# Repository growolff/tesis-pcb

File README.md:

View this project on [CADLAB.io](https://cadlab.io/project/1032). 

# tesis-pcb
Sch and Brd files of the PCBs generated in the thesis proyect.

## PSOC Pinout
PSOC CY8CKIT-059 inputs and outputs
  
| Pin | Motor | Function | A/D  | I/O |
| --- | ----- | -------- |  --- | --- |
| 12:0|   PM1 |   BRAKEN |  D   | O   |
| 12:1|   PM1 |   DIR    |  D   | O   |
| 12:2|   PM1 |   ENABLE |  D   | O   |
| 3:0 |   PM1 |   SPEED  |  A   | O   |
| 0:0 |   PM1 |   TENSION|  A   | I   |
| 2:4 |   PM1 |   HA     |  D   | I   | 
| 2:5 |   PM1 |   HB     |  D   | I   |
| 1:4 |   PM2 |   BRAKEN |  D   | O   |
| 1:5 |   PM2 |   DIR    |  D   | O   |
| 1:6 |   PM2 |   ENABLE |  D   | O   |
| 3:1 |   PM2 |   SPEED  |  A   | O   |
| 2:6 |   PM2 |   HA     |  D   | I   | 
| 2:7 |   PM2 |   HB     |  D   | I   |

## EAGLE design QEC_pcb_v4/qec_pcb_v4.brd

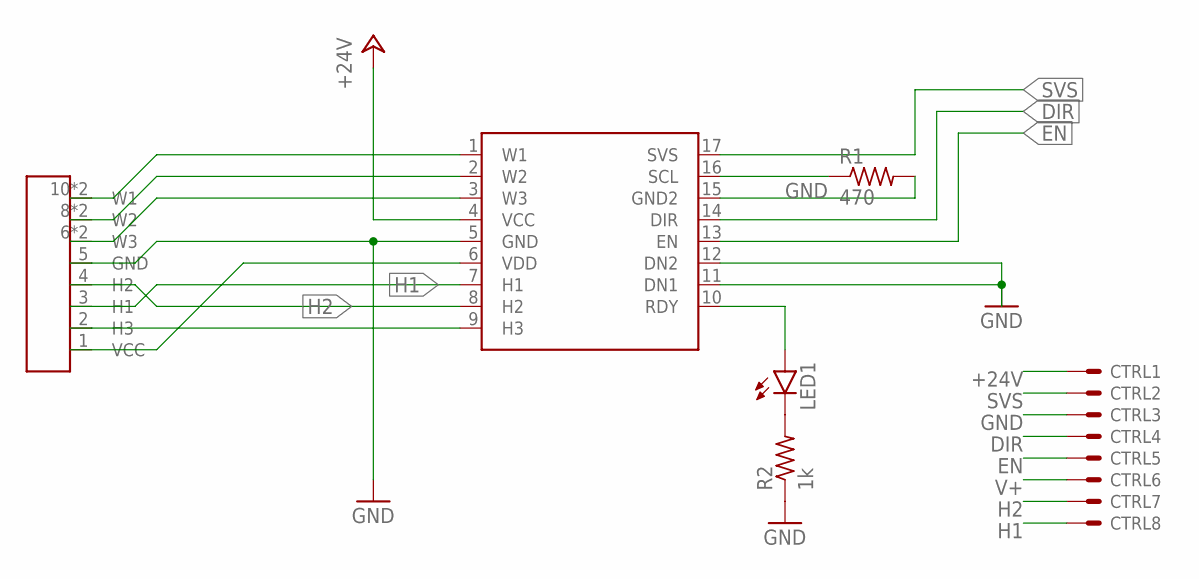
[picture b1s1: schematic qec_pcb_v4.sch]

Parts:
CTRL: JST8; JST
DEC: 1-Q-EC1-Q-EC-SMD; 1-Q-EC-SMD
LED1: LEDCHIPLED_0805; CHIPLED_0805
MOTOR: 68611114122
R1: 470; M0805
R2: 1k; M0805

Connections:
+24V: CTRL.1, DEC.4 (VCC)
DIR: CTRL.4, DEC.14 (DIR)
EN: CTRL.5, DEC.13 (EN)
GND: CTRL.3, DEC.5 (GND), DEC.11 (DN1), DEC.12 (DN2), DEC.15 (GND2), MOTOR.5 (GND), R1.2, R2.1
H1: CTRL.8, DEC.7 (H1), MOTOR.3 (H1)
H2: CTRL.7, DEC.8 (H2), MOTOR.4 (H2)
unnamed: LED1.C, R2.2
unnamed: DEC.10 (RDY), LED1.A
unnamed: DEC.1 (W1), MOTOR.10 (W1), MOTOR.11 (W1)
unnamed: DEC.16 (SCL), R1.1
unnamed: DEC.2 (W2), MOTOR.8 (W2), MOTOR.9 (W2)
unnamed: DEC.3 (W3), MOTOR.6 (W3), MOTOR.7 (W3)
unnamed: DEC.9 (H3), MOTOR.2 (H3)
SVS: CTRL.2, DEC.17 (SVS)
V+: CTRL.6, DEC.6 (VDD), MOTOR.1 (VCC)

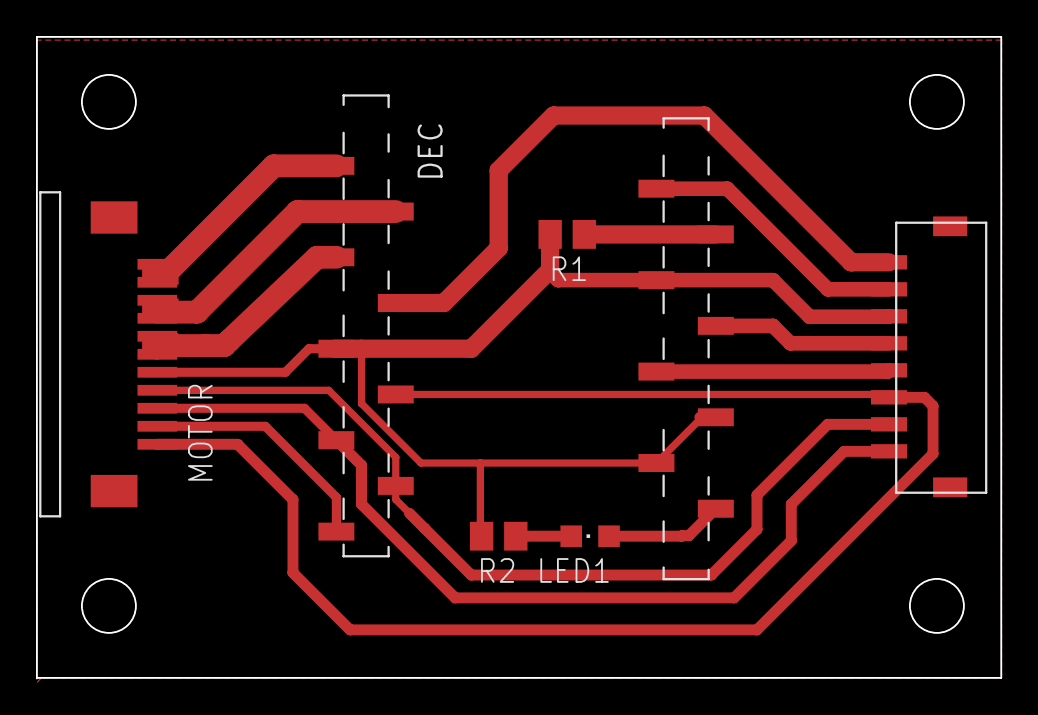
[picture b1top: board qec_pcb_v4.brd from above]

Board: 2 copper layers, 53.6 x 35.6 mm, 6 parts (0 on the bottom side), 15 nets.

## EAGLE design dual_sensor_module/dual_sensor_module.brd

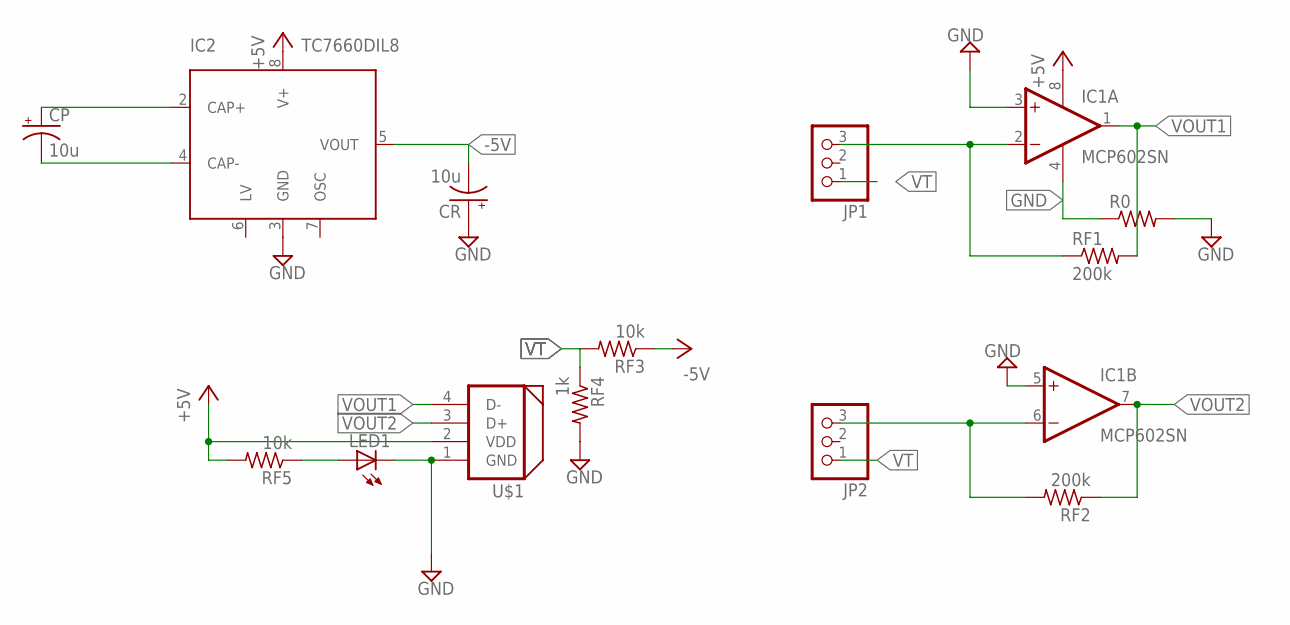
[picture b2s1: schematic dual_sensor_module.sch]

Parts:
CP: 10u; E2,5-5
CR: 10u; E2,5-5
IC1: MCP602SN; SO08
IC2: TC7660DIL8; DIL8
JP1, JP2: PINHD-1X3; 1X03
LED1: LEDCHIPLED_0805; CHIPLED_0805
R0: R-US_R1206; R1206
RF1, RF2: 200k; R0805
RF3, RF5: 10k; R0805
RF4: 1k; R0805
U$1: DYNAMIXEL_RS485; DYNAMIXEL_SPOX_04

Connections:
+5V: IC1.8 (V+), IC2.8 (V+), RF5.2, U$1.2 (VDD)
-5V: CR.-, IC2.5 (VOUT), RF3.1
GND: CR.+, IC1.3 (+IN), IC1.4 (V-), IC1.5 (+IN), IC2.3 (GND), LED1.C, R0.1, R0.2, RF4.2, U$1.1 (GND)
unnamed: CP.+, IC2.2 (CAP+)
unnamed: CP.-, IC2.4 (CAP-)
unnamed: LED1.A, RF5.1
unnamed: IC1.2 (-IN), JP1.3, RF1.1
unnamed: IC1.6 (-IN), JP2.3, RF2.2
VOUT1: IC1.1 (OUT), RF1.2, U$1.4 (D-)
VOUT2: IC1.7 (OUT), RF2.1, U$1.3 (D+)
VT: JP1.1, JP2.1, RF3.2, RF4.1

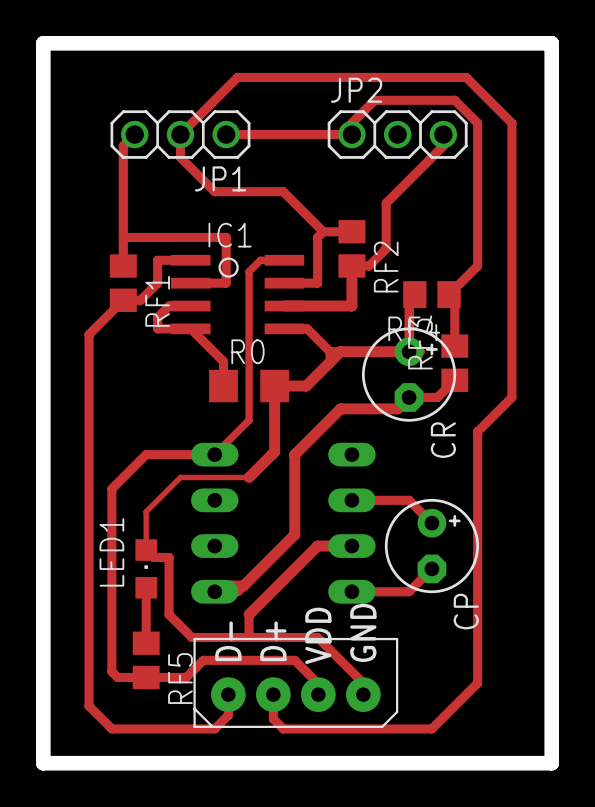
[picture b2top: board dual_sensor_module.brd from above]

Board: 2 copper layers, 28.2 x 40.0 mm, 14 parts (1 on the bottom side), 11 nets.

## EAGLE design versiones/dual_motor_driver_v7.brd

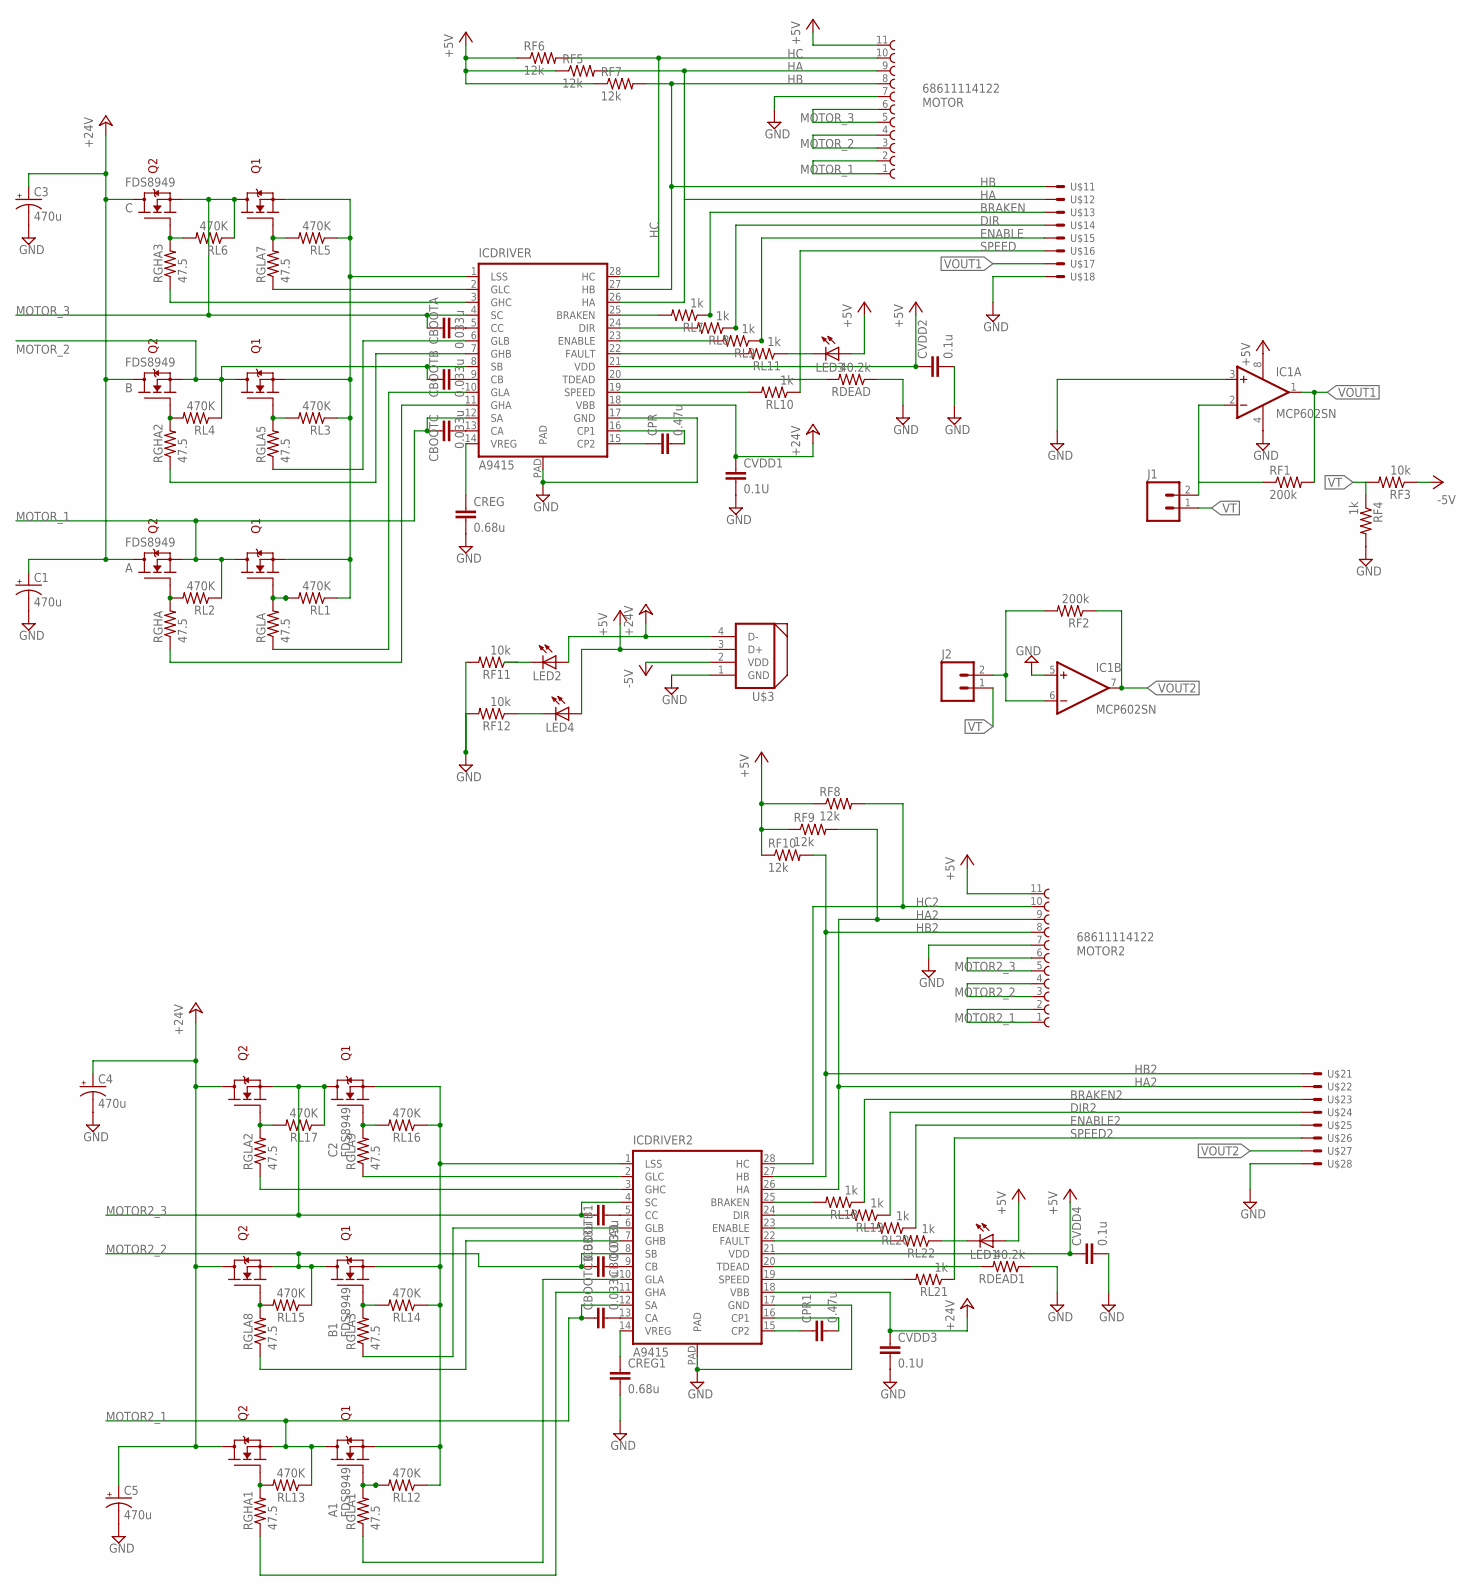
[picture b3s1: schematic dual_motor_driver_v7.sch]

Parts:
A, A1: FDS8949; SOIC8
B, B1: FDS8949; SOIC8
C, C2: FDS8949; SOIC8
C1, C3, C4, C5: 470u; 140CLH-1010
CBOOTA, CBOOTA1: 0.033u; C0805
CBOOTB, CBOOTB1: 0.033u; C0805
CBOOTC, CBOOTC1: 0.033u; C0805
CPR, CPR1: 0.47u; C0805
CREG, CREG1: 0.68u; C0805
CVDD1, CVDD3: 0.1U; C0805
CVDD2, CVDD4: 0.1u; C0805
IC1: MCP602SN; SO08
ICDRIVER, ICDRIVER2: A9415; TSSOP28
J1, J2: M02PTH; 1X02
LED1, LED2, LED3, LED4: LEDCHIPLED_0805; CHIPLED_0805
MOTOR, MOTOR2: 68611114122
RDEAD, RDEAD1: 40.2k; R0805
RF1, RF2: 200k; R0805
RF3, RF11, RF12: 10k; R0805
RF4: 1k; R0805
RF5, RF6, RF7, RF8, RF9, RF10: 12k; R0805
RGHA, RGHA1, RGHA2, RGHA3: 47.5; R0805
RGLA, RGLA1, RGLA2, RGLA3, RGLA5, RGLA7, RGLA8, RGLA9: 47.5; R0805
RL1, RL2, RL3, RL4, RL5, RL6, RL12, RL13, RL14, RL15, RL16, RL17: 470K; R0805
RL7, RL8, RL9, RL10, RL11, RL18, RL19, RL20, RL21, RL22: 1k; R0805
U$1, U$2: JST8; JST
U$3: DYNAMIXEL_RS485; DYNAMIXEL_SPOX_04

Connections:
+5V: CVDD2.1, CVDD4.1, IC1.8 (V+), ICDRIVER.21 (VDD), ICDRIVER2.21 (VDD), LED1.A, LED3.A, LED4.A, MOTOR.11, MOTOR2.11, RF5.1, RF6.1, RF7.1, RF8.1, RF9.1, RF10.1, U$3.3 (D+)
+24V: A.5 (D2), A.6 (D2), A1.5 (D2), A1.6 (D2), B.5 (D2), B.6 (D2), B1.5 (D2), B1.6 (D2), C.5 (D2), C.6 (D2), C1.+, C2.5 (D2), C2.6 (D2), C3.+, C4.+, C5.+, CVDD1.1, CVDD3.1, ICDRIVER.18 (VBB), ICDRIVER2.18 (VBB), LED2.A, U$3.4 (D-)
-5V: RF3.1, U$3.2 (VDD)
BRAKEN: RL7.1, U$1.3
BRAKEN2: RL18.1, U$2.3
DIR: RL8.1, U$1.4
DIR2: RL19.1, U$2.4
ENABLE: RL9.1, U$1.5
ENABLE2: RL20.1, U$2.5
GND: A.1 (S1), A1.1 (S1), B.1 (S1), B1.1 (S1), C.1 (S1), C1.-, C2.1 (S1), C3.-, C4.-, C5.-, CREG.2, CREG1.2, CVDD1.2, CVDD2.2, CVDD3.2, CVDD4.2, IC1.3 (+IN), IC1.4 (V-), IC1.5 (+IN), ICDRIVER.1 (LSS), ICDRIVER.17 (GND), ICDRIVER.PAD, ICDRIVER2.1 (LSS), ICDRIVER2.17 (GND), ICDRIVER2.PAD, MOTOR.7, MOTOR2.7, RDEAD.1, RDEAD1.1, RF4.2, RF11.2, RF12.2, RL1.1, RL3.1, RL5.1, RL12.1, RL14.1, RL16.1, U$1.8, U$2.8, U$3.1 (GND)
HA: ICDRIVER.26 (HA), MOTOR.9, RF5.2, U$1.2
HA2: ICDRIVER2.26 (HA), MOTOR2.9, RF9.2, U$2.2
HB: ICDRIVER.27 (HB), MOTOR.8, RF7.2, U$1.1
HB2: ICDRIVER2.27 (HB), MOTOR2.8, RF10.2, U$2.1
HC: ICDRIVER.28 (HC), MOTOR.10, RF6.2
HC2: ICDRIVER2.28 (HC), MOTOR2.10, RF8.2
MOTOR2_1: A1.3 (S2), A1.7 (D1), A1.8 (D1), CBOOTC1.1, ICDRIVER2.12 (SA), MOTOR2.1, MOTOR2.2, RL13.1
MOTOR2_2: B1.3 (S2), B1.7 (D1), B1.8 (D1), CBOOTB1.1, ICDRIVER2.8 (SB), MOTOR2.3, MOTOR2.4, RL15.1
MOTOR2_3: C2.3 (S2), C2.7 (D1), C2.8 (D1), CBOOTA1.2, ICDRIVER2.4 (SC), MOTOR2.5, MOTOR2.6, RL17.1
MOTOR_1: A.3 (S2), A.7 (D1), A.8 (D1), CBOOTC.1, ICDRIVER.12 (SA), MOTOR.1, MOTOR.2, RL2.1
MOTOR_2: B.3 (S2), B.7 (D1), B.8 (D1), CBOOTB.1, ICDRIVER.8 (SB), MOTOR.3, MOTOR.4, RL4.1
MOTOR_3: C.3 (S2), C.7 (D1), C.8 (D1), CBOOTA.2, ICDRIVER.4 (SC), MOTOR.5, MOTOR.6, RL6.1
unnamed: A1.2 (G1), RGLA1.2, RL12.2
unnamed: A1.4 (G2), RGHA1.2, RL13.2
unnamed: B1.2 (G1), RGLA3.2, RL14.2
unnamed: B1.4 (G2), RGLA8.2, RL15.2
unnamed: C2.2 (G1), RGLA9.2, RL16.2
unnamed: C2.4 (G2), RGLA2.2, RL17.2
unnamed: B.2 (G1), RGLA5.2, RL3.2
unnamed: B.4 (G2), RGHA2.2, RL4.2
unnamed: ICDRIVER2.11 (GHA), RGHA1.1
unnamed: ICDRIVER2.10 (GLA), RGLA1.1
unnamed: ICDRIVER2.6 (GLB), RGLA3.1
unnamed: ICDRIVER2.7 (GHB), RGLA8.1
unnamed: CBOOTA1.1, ICDRIVER2.5 (CC)
unnamed: CBOOTB1.2, ICDRIVER2.9 (CB)
unnamed: C.2 (G1), RGLA7.2, RL5.2
unnamed: CPR.1, ICDRIVER.15 (CP2)
unnamed: ICDRIVER.11 (GHA), RGHA.1
unnamed: C.4 (G2), RGHA3.2, RL6.2
unnamed: CREG1.1, ICDRIVER2.14 (VREG)
unnamed: ICDRIVER.10 (GLA), RGLA.1
unnamed: CREG.1, ICDRIVER.14 (VREG)
unnamed: CBOOTC.2, ICDRIVER.13 (CA)
unnamed: CBOOTC1.2, ICDRIVER2.13 (CA)
unnamed: ICDRIVER.2 (GLC), RGLA7.1
unnamed: ICDRIVER.6 (GLB), RGLA5.1
unnamed: ICDRIVER.7 (GHB), RGHA2.1
unnamed: ICDRIVER.3 (GHC), RGHA3.1
unnamed: CBOOTB.2, ICDRIVER.9 (CB)
unnamed: CPR.2, ICDRIVER.16 (CP1)
unnamed: ICDRIVER2.2 (GLC), RGLA9.1
unnamed: CBOOTA.1, ICDRIVER.5 (CC)
unnamed: A.2 (G1), RGLA.2, RL1.2
unnamed: A.4 (G2), RGHA.2, RL2.2
unnamed: ICDRIVER2.3 (GHC), RGLA2.1
unnamed: CPR1.1, ICDRIVER2.15 (CP2)
unnamed: CPR1.2, ICDRIVER2.16 (CP1)
unnamed: ICDRIVER2.19 (SPEED), RL21.2
unnamed: ICDRIVER2.23 (ENABLE), RL20.2
unnamed: ICDRIVER2.24 (DIR), RL19.2
unnamed: ICDRIVER.19 (SPEED), RL10.2
unnamed: ICDRIVER.23 (ENABLE), RL9.2
unnamed: ICDRIVER.24 (DIR), RL8.2
unnamed: ICDRIVER2.25 (BRAKEN), RL18.2
unnamed: ICDRIVER.25 (BRAKEN), RL7.2
unnamed: ICDRIVER.20 (TDEAD), RDEAD.2
unnamed: ICDRIVER.22 (FAULT), RL11.2
unnamed: LED3.C, RL11.1
unnamed: LED2.C, RF11.1
unnamed: ICDRIVER2.20 (TDEAD), RDEAD1.2
unnamed: ICDRIVER2.22 (FAULT), RL22.2
unnamed: LED1.C, RL22.1
unnamed: IC1.2 (-IN), J1.2, RF1.1
unnamed: LED4.C, RF12.1
unnamed: IC1.6 (-IN), J2.2, RF2.2
SPEED: RL10.1, U$1.6
SPEED2: RL21.1, U$2.6
VOUT1: IC1.1 (OUT), RF1.2, U$1.7
VOUT2: IC1.7 (OUT), RF2.1, U$2.7
VT: J1.1, J2.1, RF3.2, RF4.1

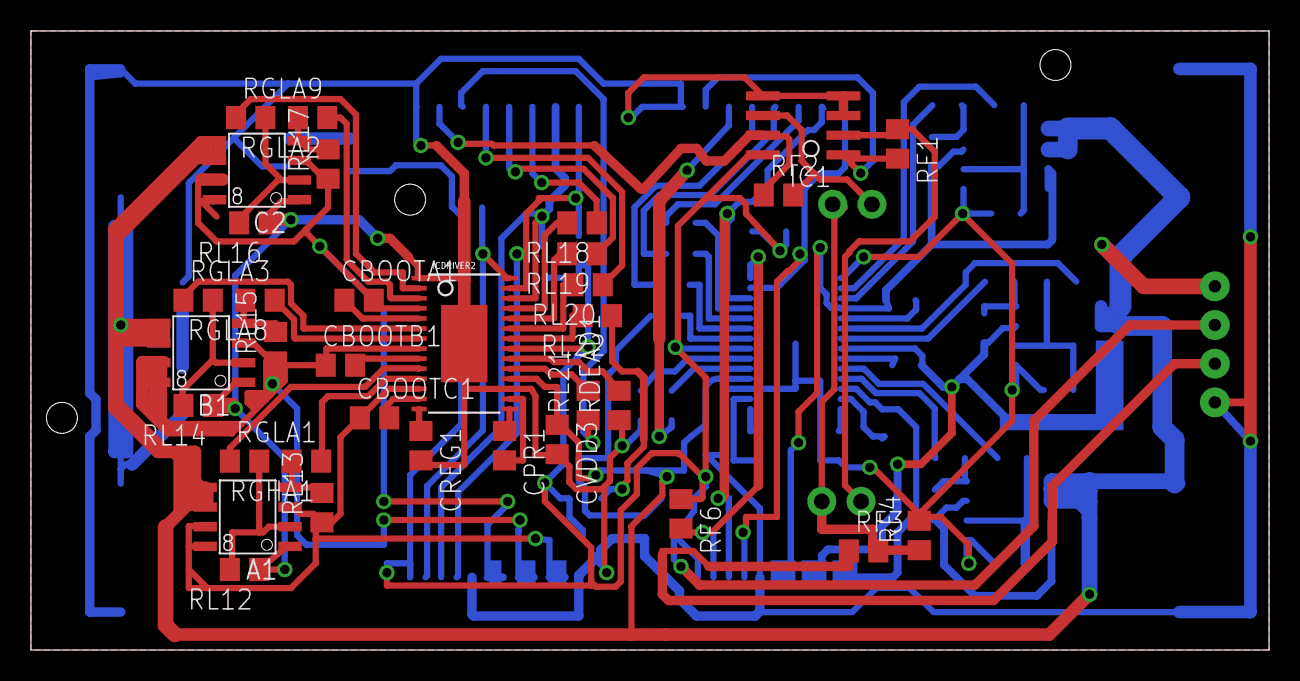
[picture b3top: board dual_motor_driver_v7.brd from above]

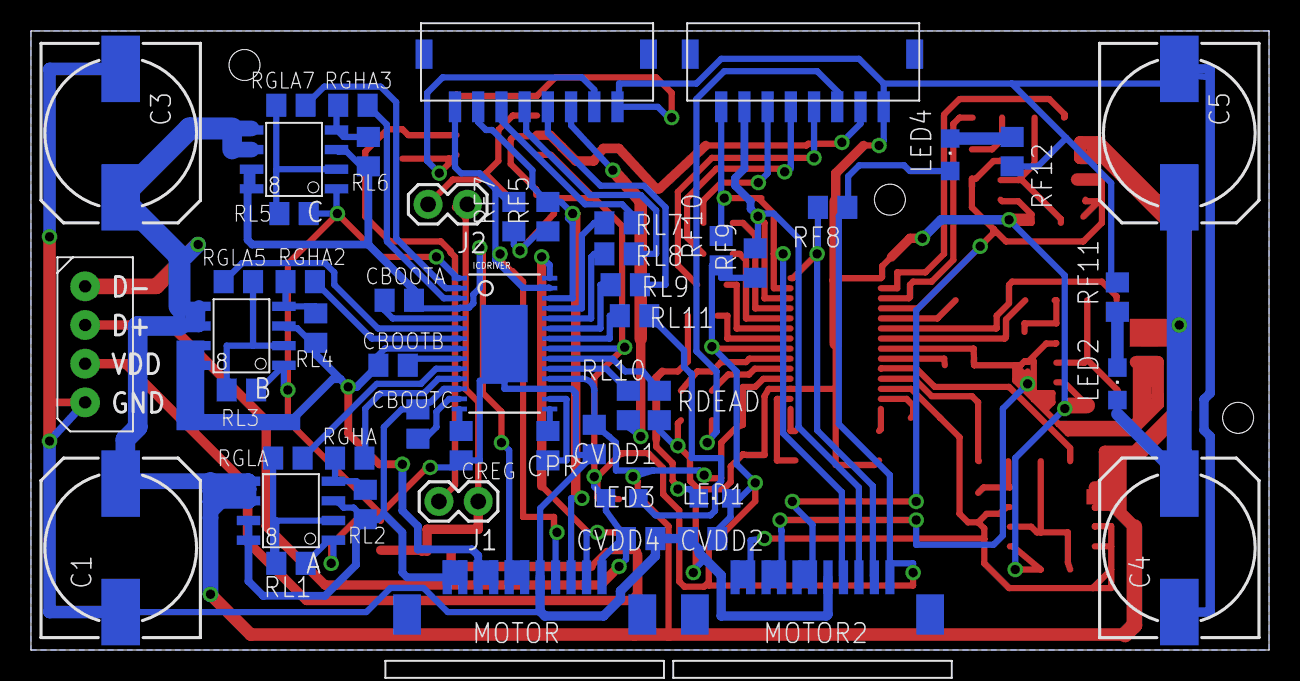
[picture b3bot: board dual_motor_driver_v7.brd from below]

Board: 2 copper layers, 80.0 x 40.0 mm, 86 parts (52 on the bottom side), 81 nets.

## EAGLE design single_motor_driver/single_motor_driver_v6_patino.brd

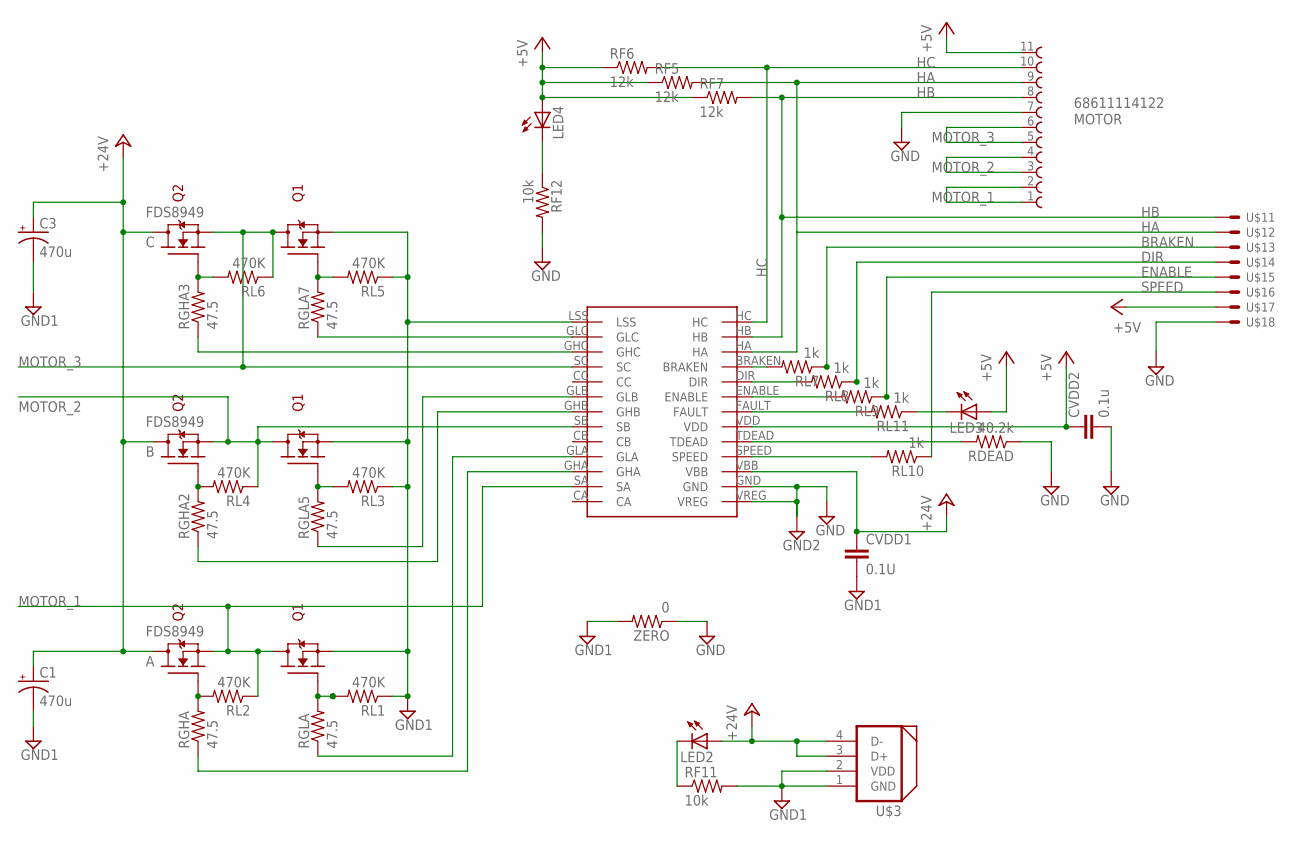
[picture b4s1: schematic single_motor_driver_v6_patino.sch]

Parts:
A: FDS8949; SOIC8
B: FDS8949; SOIC8
C: FDS8949; SOIC8
C1, C3: 470u; 140CLH-1010
CVDD1: 0.1U; C0805
CVDD2: 0.1u; C0805
LED2, LED3, LED4: LEDCHIPLED_0805; CHIPLED_0805
MOTOR: 68611114122
RDEAD: 40.2k; R0805
RF5, RF6, RF7: 12k; R0805
RF11, RF12: 10k; R0805
RGHA, RGHA2, RGHA3: 47.5; R0805
RGLA, RGLA5, RGLA7: 47.5; R0805
RL1, RL2, RL3, RL4, RL5, RL6: 470K; R0805
RL7, RL8, RL9, RL10, RL11: 1k; R0805
U$1: JST8; JST
U$2: TSSOP28-BRK
U$3: DYNAMIXEL_RS485; DYNAMIXEL_SPOX_04
ZERO: 0; R0805

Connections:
+5V: CVDD2.1, LED3.A, LED4.A, MOTOR.11, RF5.1, RF6.1, RF7.1, U$1.7, U$2.VDD
+24V: A.5 (D2), A.6 (D2), B.5 (D2), B.6 (D2), C.5 (D2), C.6 (D2), C1.+, C3.+, CVDD1.1, LED2.A, U$2.VBB, U$3.3 (D+), U$3.4 (D-)
BRAKEN: RL7.1, U$1.3
DIR: RL8.1, U$1.4
ENABLE: RL9.1, U$1.5
GND: CVDD2.2, MOTOR.7, RDEAD.1, RF12.2, U$1.8, U$2.GND, U$2.VREG, ZERO.1
HA: MOTOR.9, RF5.2, U$1.2, U$2.HA
HB: MOTOR.8, RF7.2, U$1.1, U$2.HB
HC: MOTOR.10, RF6.2, U$2.HC
MOTOR_1: A.3 (S2), A.7 (D1), A.8 (D1), MOTOR.1, MOTOR.2, RL2.1, U$2.SA
MOTOR_2: B.3 (S2), B.7 (D1), B.8 (D1), MOTOR.3, MOTOR.4, RL4.1, U$2.SB
MOTOR_3: C.3 (S2), C.7 (D1), C.8 (D1), MOTOR.5, MOTOR.6, RL6.1, U$2.SC
unnamed: B.2 (G1), RGLA5.2, RL3.2
unnamed: B.4 (G2), RGHA2.2, RL4.2
unnamed: C.2 (G1), RGLA7.2, RL5.2
unnamed: RGHA.1, U$2.GHA
unnamed: C.4 (G2), RGHA3.2, RL6.2
unnamed: RGLA.1, U$2.GLA
unnamed: RGLA7.1, U$2.GLC
unnamed: RGLA5.1, U$2.GLB
unnamed: RGHA2.1, U$2.GHB
unnamed: RGHA3.1, U$2.GHC
unnamed: A.2 (G1), RGLA.2, RL1.2
unnamed: A.4 (G2), RGHA.2, RL2.2
unnamed: RL10.2, U$2.SPEED
unnamed: RL9.2, U$2.ENABLE
unnamed: RL8.2, U$2.DIR
unnamed: RL7.2, U$2.BRAKEN
unnamed: RDEAD.2, U$2.TDEAD
unnamed: RL11.2, U$2.FAULT
unnamed: LED3.C, RL11.1
unnamed: LED2.C, RF11.1
unnamed: LED4.C, RF12.1
PGND: A.1 (S1), B.1 (S1), C.1 (S1), C1.-, C3.-, CVDD1.2, RF11.2, RL1.1, RL3.1, RL5.1, U$2.LSS, U$3.1 (GND), U$3.2 (VDD), ZERO.2
SPEED: RL10.1, U$1.6

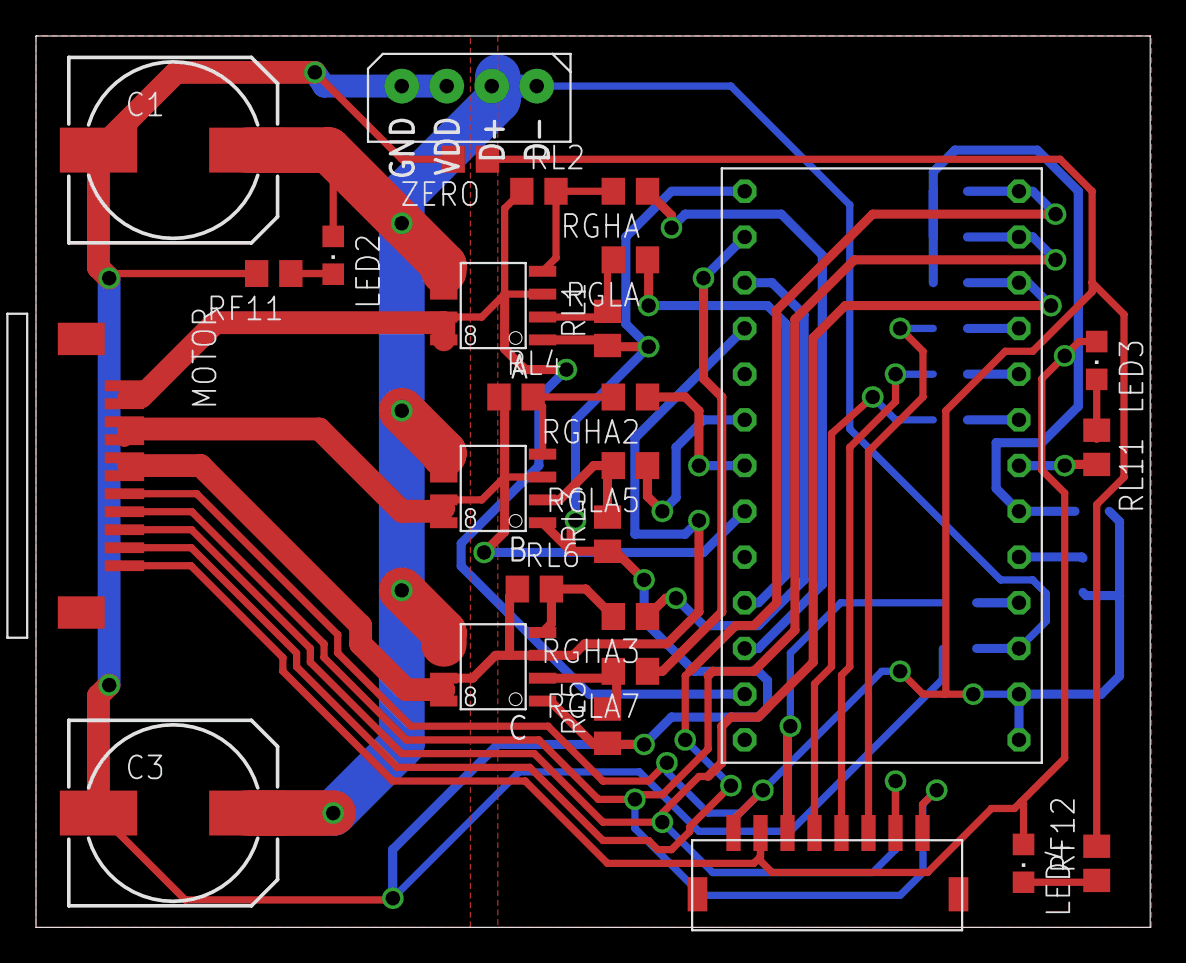
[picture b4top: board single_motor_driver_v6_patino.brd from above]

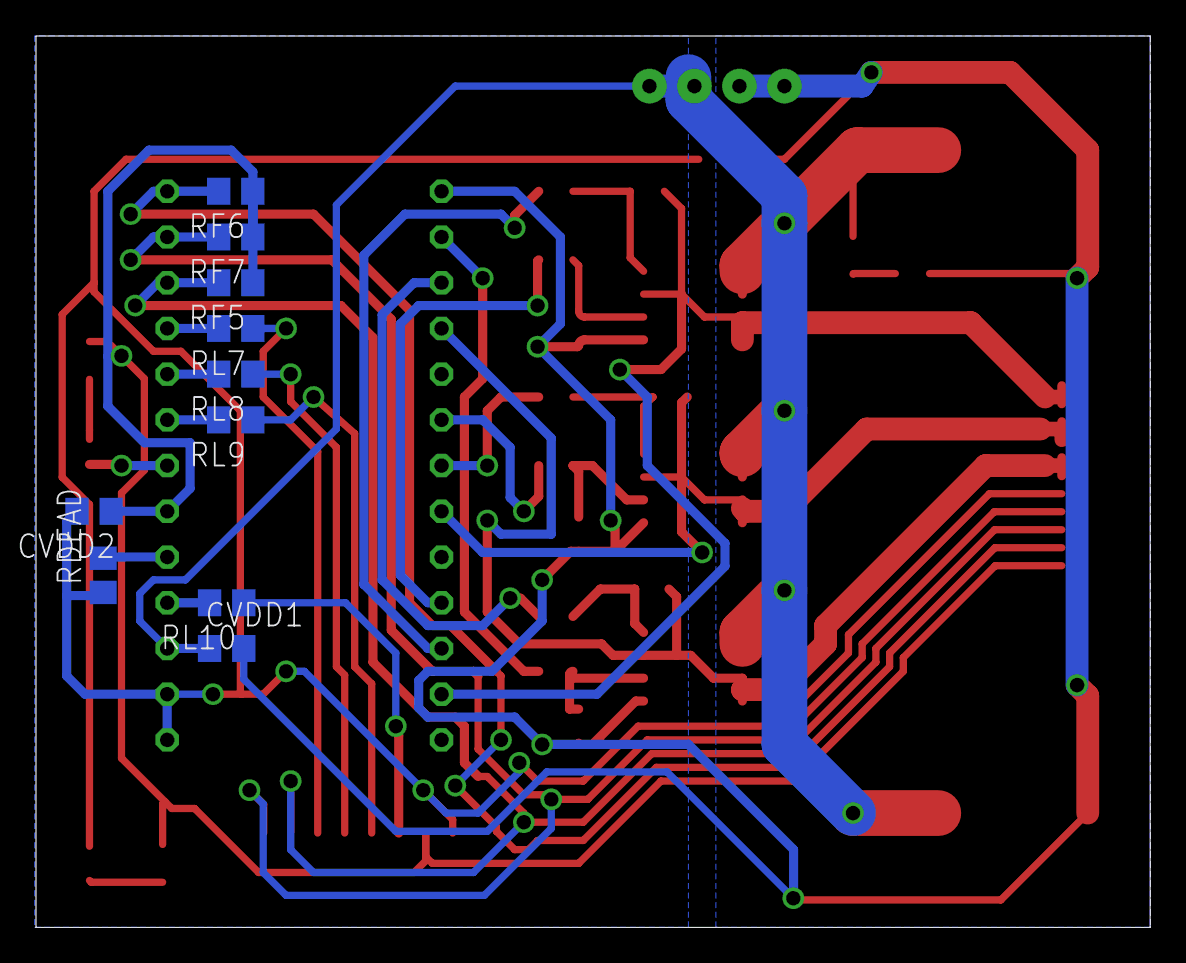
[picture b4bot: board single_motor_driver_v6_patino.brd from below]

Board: 2 copper layers, 61.9 x 49.5 mm, 38 parts (10 on the bottom side), 35 nets.

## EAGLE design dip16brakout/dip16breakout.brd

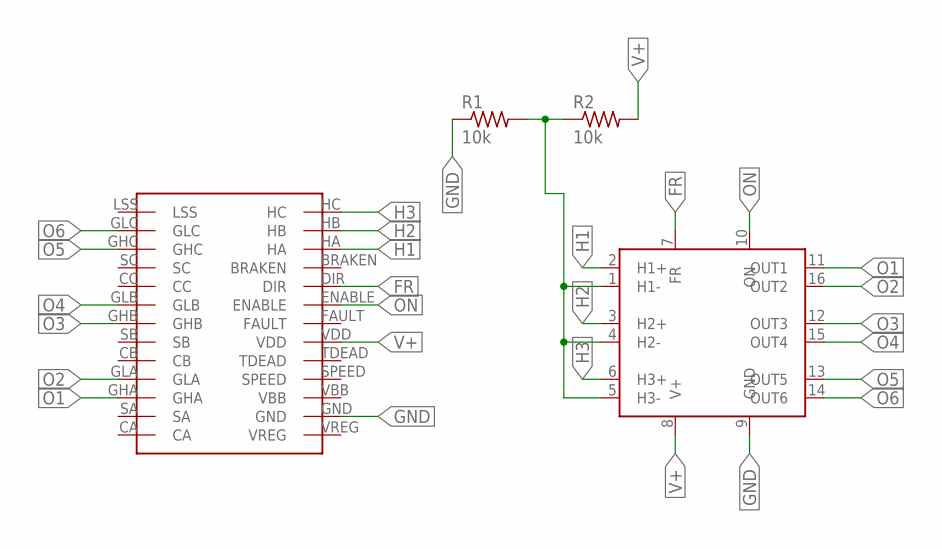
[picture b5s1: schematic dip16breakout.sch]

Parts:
R1, R2: 10k; R0805
U$1: NJM2624A; DMP16
U$2: TSSOP28-BRK

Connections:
FR: U$1.7 (FR), U$2.DIR
GND: R1.1, U$1.9 (GND), U$2.GND
H1: U$1.2 (H1+), U$2.HA
H2: U$1.3 (H2+), U$2.HB
H3: U$1.6 (H3+), U$2.HC
unnamed: R1.2, R2.1, U$1.1 (H1-), U$1.4 (H2-), U$1.5 (H3-)
O1: U$1.11 (OUT1), U$2.GHA
O2: U$1.16 (OUT2), U$2.GLA
O3: U$1.12 (OUT3), U$2.GHB
O4: U$1.15 (OUT4), U$2.GLB
O5: U$1.13 (OUT5), U$2.GHC
O6: U$1.14 (OUT6), U$2.GLC
ON: U$1.10 (ON), U$2.ENABLE
V+: R2.2, U$1.8 (V+), U$2.VDD

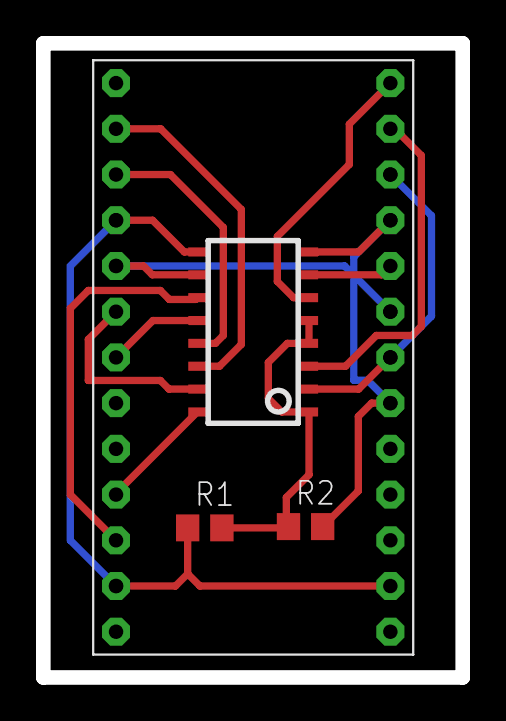
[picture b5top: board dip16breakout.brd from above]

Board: 2 copper layers, 23.3 x 35.2 mm, 4 parts (0 on the bottom side), 14 nets.

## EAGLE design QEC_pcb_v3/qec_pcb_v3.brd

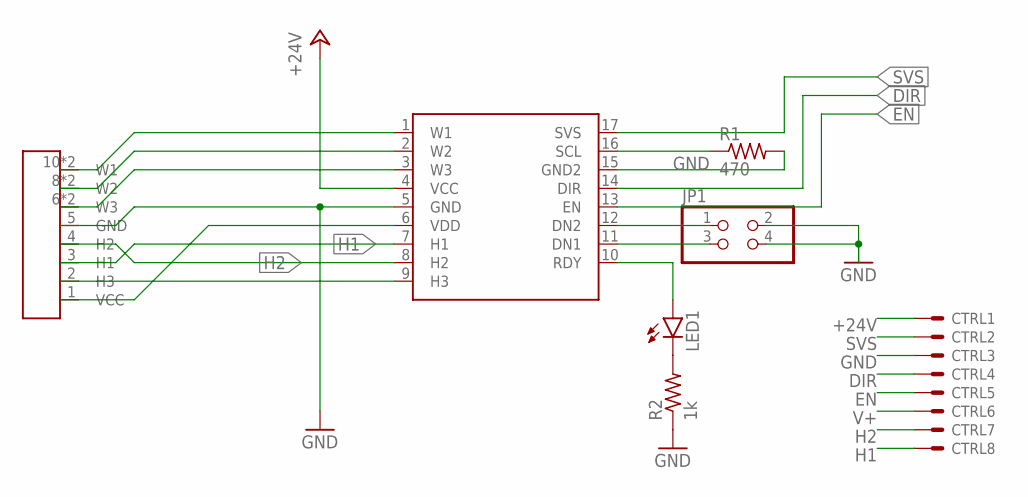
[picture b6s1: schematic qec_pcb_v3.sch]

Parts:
CTRL: JST8; JST
JP1: PINHD-2X2; 2X02
K1: 68611114122
LED1: LEDCHIPLED_0805; CHIPLED_0805
R1: 470; M0805
R2: 1k; M0805
U$1: 1-Q-EC1-Q-EC-SMD; 1-Q-EC-SMD

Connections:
+24V: CTRL.1, U$1.4 (VCC)
DIR: CTRL.4, U$1.14 (DIR)
EN: CTRL.5, U$1.13 (EN)
GND: CTRL.3, JP1.2, JP1.4, K1.5 (GND), R1.2, R2.1, U$1.5 (GND), U$1.15 (GND2)
H1: CTRL.8, K1.3 (H1), U$1.7 (H1)
H2: CTRL.7, K1.4 (H2), U$1.8 (H2)
unnamed: LED1.C, R2.2
unnamed: LED1.A, U$1.10 (RDY)
unnamed: JP1.1, U$1.12 (DN2)
unnamed: JP1.3, U$1.11 (DN1)
unnamed: K1.10 (W1), K1.11 (W1), U$1.1 (W1)
unnamed: R1.1, U$1.16 (SCL)
unnamed: K1.8 (W2), K1.9 (W2), U$1.2 (W2)
unnamed: K1.6 (W3), K1.7 (W3), U$1.3 (W3)
unnamed: K1.2 (H3), U$1.9 (H3)
SVS: CTRL.2, U$1.17 (SVS)
V+: CTRL.6, K1.1 (VCC), U$1.6 (VDD)

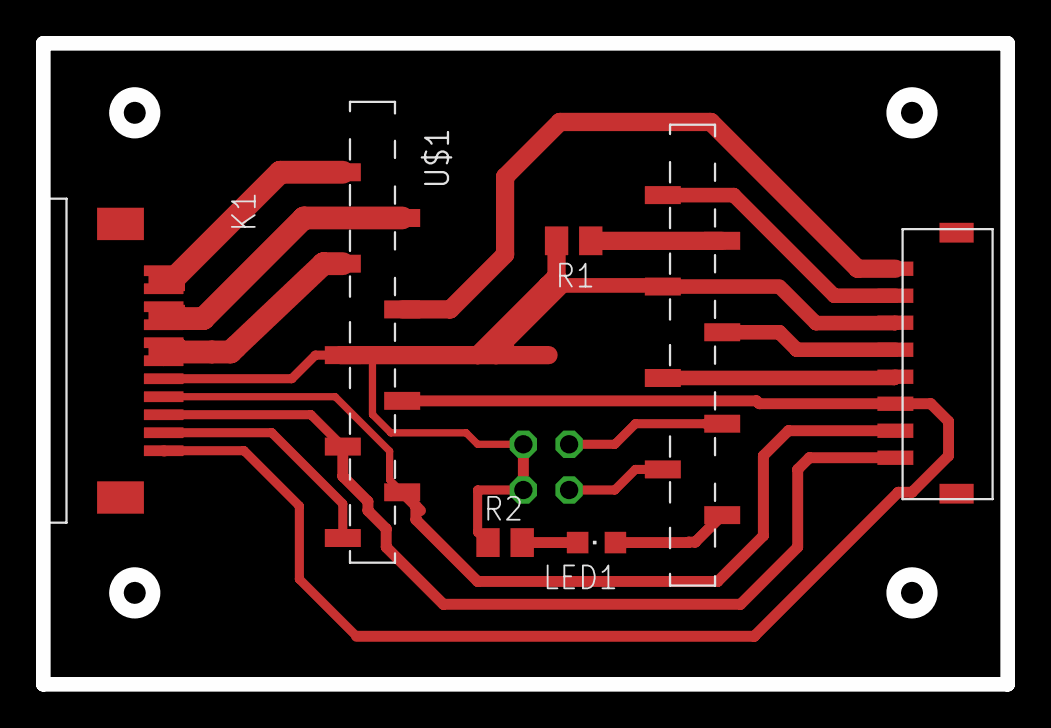
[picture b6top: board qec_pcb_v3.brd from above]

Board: 2 copper layers, 53.6 x 35.6 mm, 7 parts (1 on the bottom side), 17 nets.

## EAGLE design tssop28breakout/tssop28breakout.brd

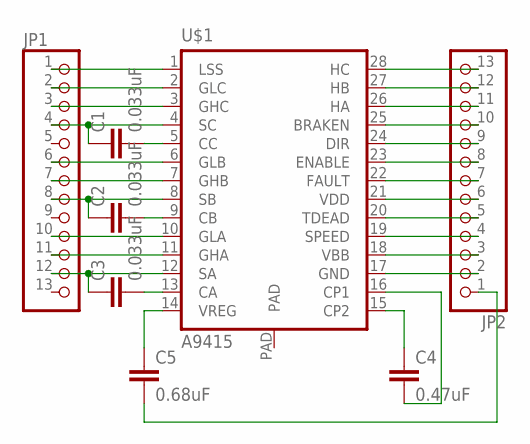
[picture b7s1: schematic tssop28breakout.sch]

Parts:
C1, C2, C3: 0.033uF; C0805
C4: 0.47uF; C0805
C5: 0.68uF; C0805
JP1, JP2: PINHD-1X13_BIG; 1X13-BIG
U$1: A9415; TSSOP28

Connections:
BRAKEN: JP2.10, U$1.25 (BRAKEN)
CA: C3.2, U$1.13 (CA)
CB: C2.2, U$1.9 (CB)
CC: C1.2, U$1.5 (CC)
DIR: JP2.9, U$1.24 (DIR)
ENABLE: JP2.8, U$1.23 (ENABLE)
FAULT: JP2.7, U$1.22 (FAULT)
GHA: JP1.11, U$1.11 (GHA)
GHB: JP1.7, U$1.7 (GHB)
GHC: JP1.3, U$1.3 (GHC)
GLA: JP1.10, U$1.10 (GLA)
GLB: JP1.6, U$1.6 (GLB)
GLC: JP1.2, U$1.2 (GLC)
GND: JP2.2, U$1.17 (GND)
HA: JP2.11, U$1.26 (HA)
HB: JP2.12, U$1.27 (HB)
HC: JP2.13, U$1.28 (HC)
LSS: JP1.1, U$1.1 (LSS)
unnamed: C4.1, U$1.15 (CP2)
unnamed: C4.2, U$1.16 (CP1)
PAD: U$1.PAD
SA: C3.1, JP1.12, U$1.12 (SA)
SB: C2.1, JP1.8, U$1.8 (SB)
SC: C1.1, JP1.4, U$1.4 (SC)
SPEED: JP2.4, U$1.19 (SPEED)
TDEAD: JP2.5, U$1.20 (TDEAD)
VBB: JP2.3, U$1.18 (VBB)
VDD: JP2.6, U$1.21 (VDD)
VREG: C5.1, U$1.14 (VREG)
VREG_GND: C5.2, JP2.1

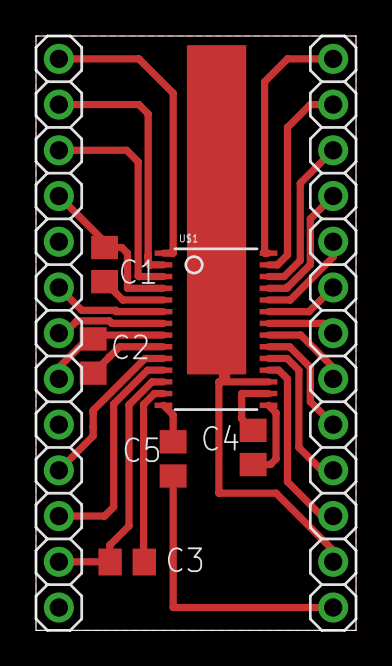
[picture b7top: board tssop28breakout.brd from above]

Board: 2 copper layers, 17.8 x 33.0 mm, 8 parts (0 on the bottom side), 29 nets.

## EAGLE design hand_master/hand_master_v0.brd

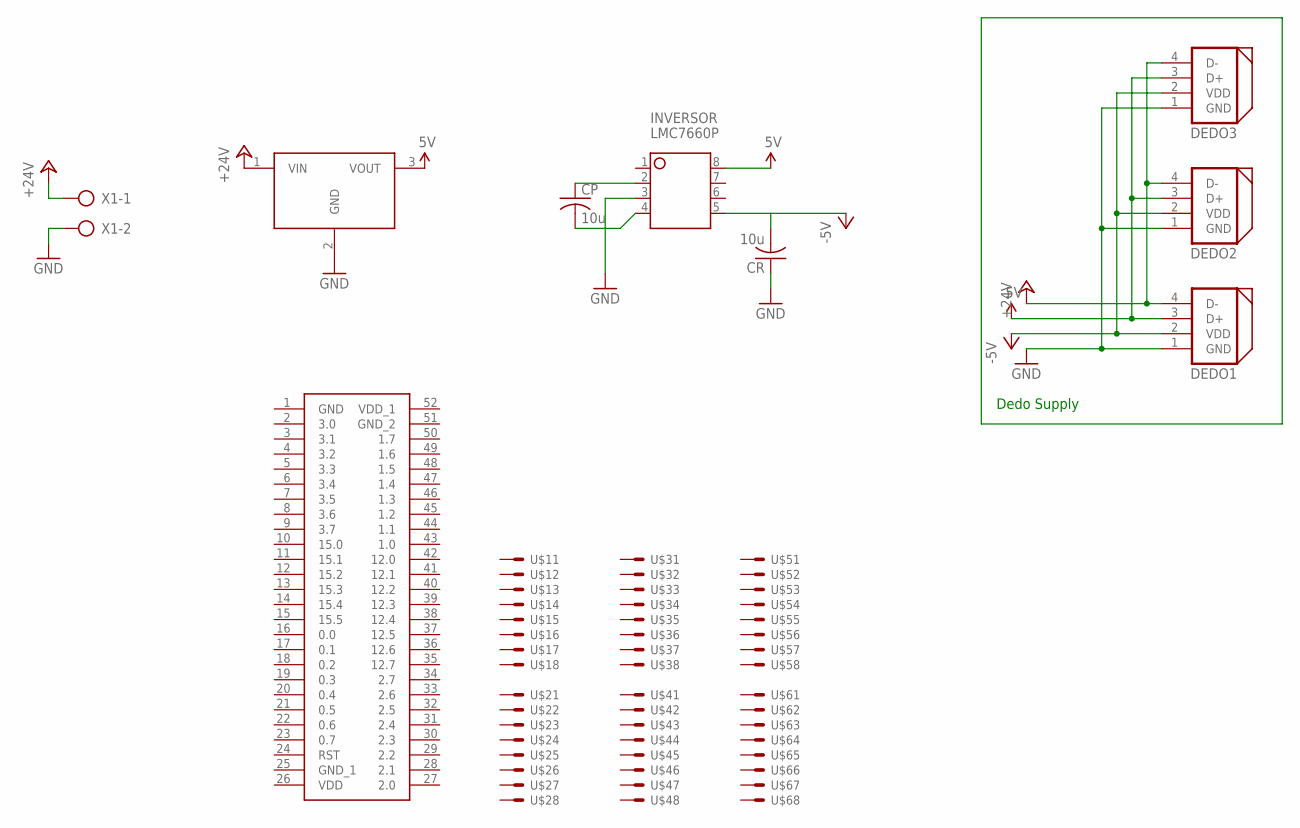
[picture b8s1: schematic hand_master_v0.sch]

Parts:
CP: 10u; C025-025X050
CR: 10u; C025-025X050
DEDO1, DEDO2, DEDO3: DYNAMIXEL_RS485; DYNAMIXEL_SPOX_04
INVERSOR: LMC7660P; DIL08
POWER_SUPPLY: TSR-1; TO220V
U$1, U$2, U$3, U$4, U$5, U$6: JST8; JST
U$7: CY8CKIT-059
X1: AK500/2

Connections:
5V: DEDO1.3 (D+), DEDO2.3 (D+), DEDO3.3 (D+), INVERSOR.8 (V+), POWER_SUPPLY.3 (VOUT)
+24V: DEDO1.4 (D-), DEDO2.4 (D-), DEDO3.4 (D-), POWER_SUPPLY.1 (VIN), X1.1
-5V: CR.2, DEDO1.2 (VDD), DEDO2.2 (VDD), DEDO3.2 (VDD), INVERSOR.5 (VOUT)
GND: CR.1, DEDO1.1 (GND), DEDO2.1 (GND), DEDO3.1 (GND), INVERSOR.3 (GND), POWER_SUPPLY.2 (GND), X1.2
unnamed: CP.1, INVERSOR.2 (CAP+)
unnamed: CP.2, INVERSOR.4 (CAP-)

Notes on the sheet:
Dedo Supply

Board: 2 copper layers, 15 parts (0 on the bottom side), 6 nets, no tracks yet.

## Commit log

2017-10-19 dual_motor_driver version 6 and hand_master version 0
2017-11-24 fixed tension sensor amplifier
2017-12-28 added A4915 breakout
2017-12-28 first version of single motor driver
2017-12-29 last version finished, pls work!
2018-05-15 last update, working
2018-05-15 Backlink to CADLAB.io has been added.
2018-05-18 updated pinout table
2018-10-24 adedd 1-Q-EC test board
2018-10-24 minor changes and ready to route
2018-12-13 version nueva de la pcb de los drivers. Utiliza conectores jst 1.5mm de 8 pines
2019-06-28 version dos actualizada
2019-06-28 versión 3 control 1 motor
2019-06-28 modulo para dos sensores de fuerza v1
2019-06-28 archivos de prueba antiguos
2019-06-28 robot hand eagle lib
2019-06-28 agregado plano de tierra y modificadas las imagenes para corte
2019-08-22 archivos ordenados y dedo.lbr -> robot_hand.lbr actualizado
2020-10-05 ultima version motor controller
2020-10-05 update library
2020-10-05 last fix
2021-08-26 update directories
2021-08-26 update files

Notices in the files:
parts and their libraries:
SparkFun-Aesthetics: Licensing: Creative Commons ShareAlike 4.0 International - https://creativecommons.org/licenses/by-sa/4.0
FPC_Connectors_Flat_Flexible_Cable_rev15: Copyright: Würth Elektronik
